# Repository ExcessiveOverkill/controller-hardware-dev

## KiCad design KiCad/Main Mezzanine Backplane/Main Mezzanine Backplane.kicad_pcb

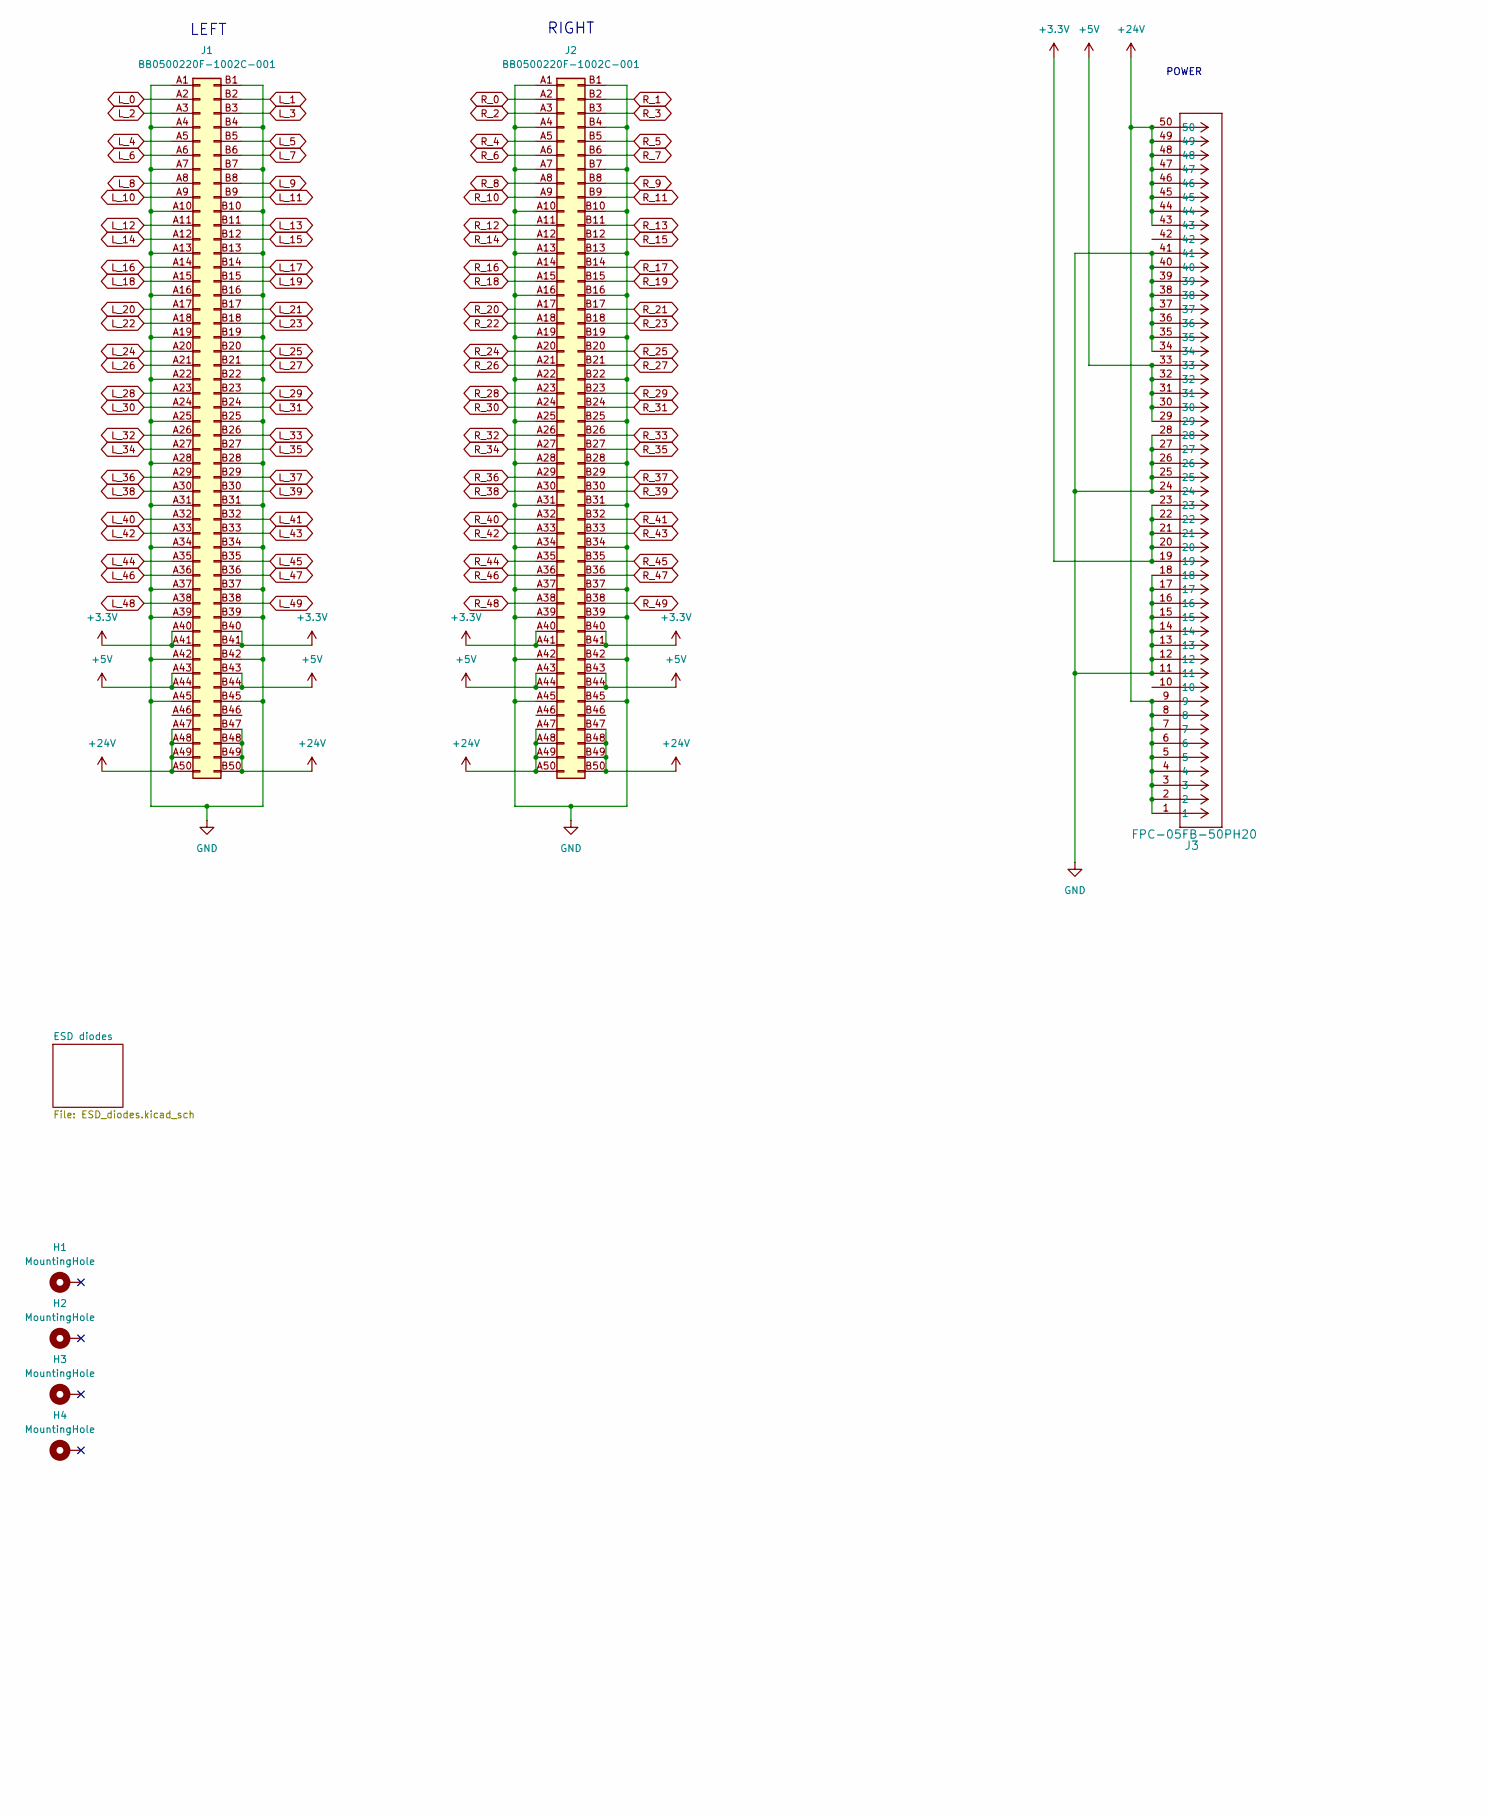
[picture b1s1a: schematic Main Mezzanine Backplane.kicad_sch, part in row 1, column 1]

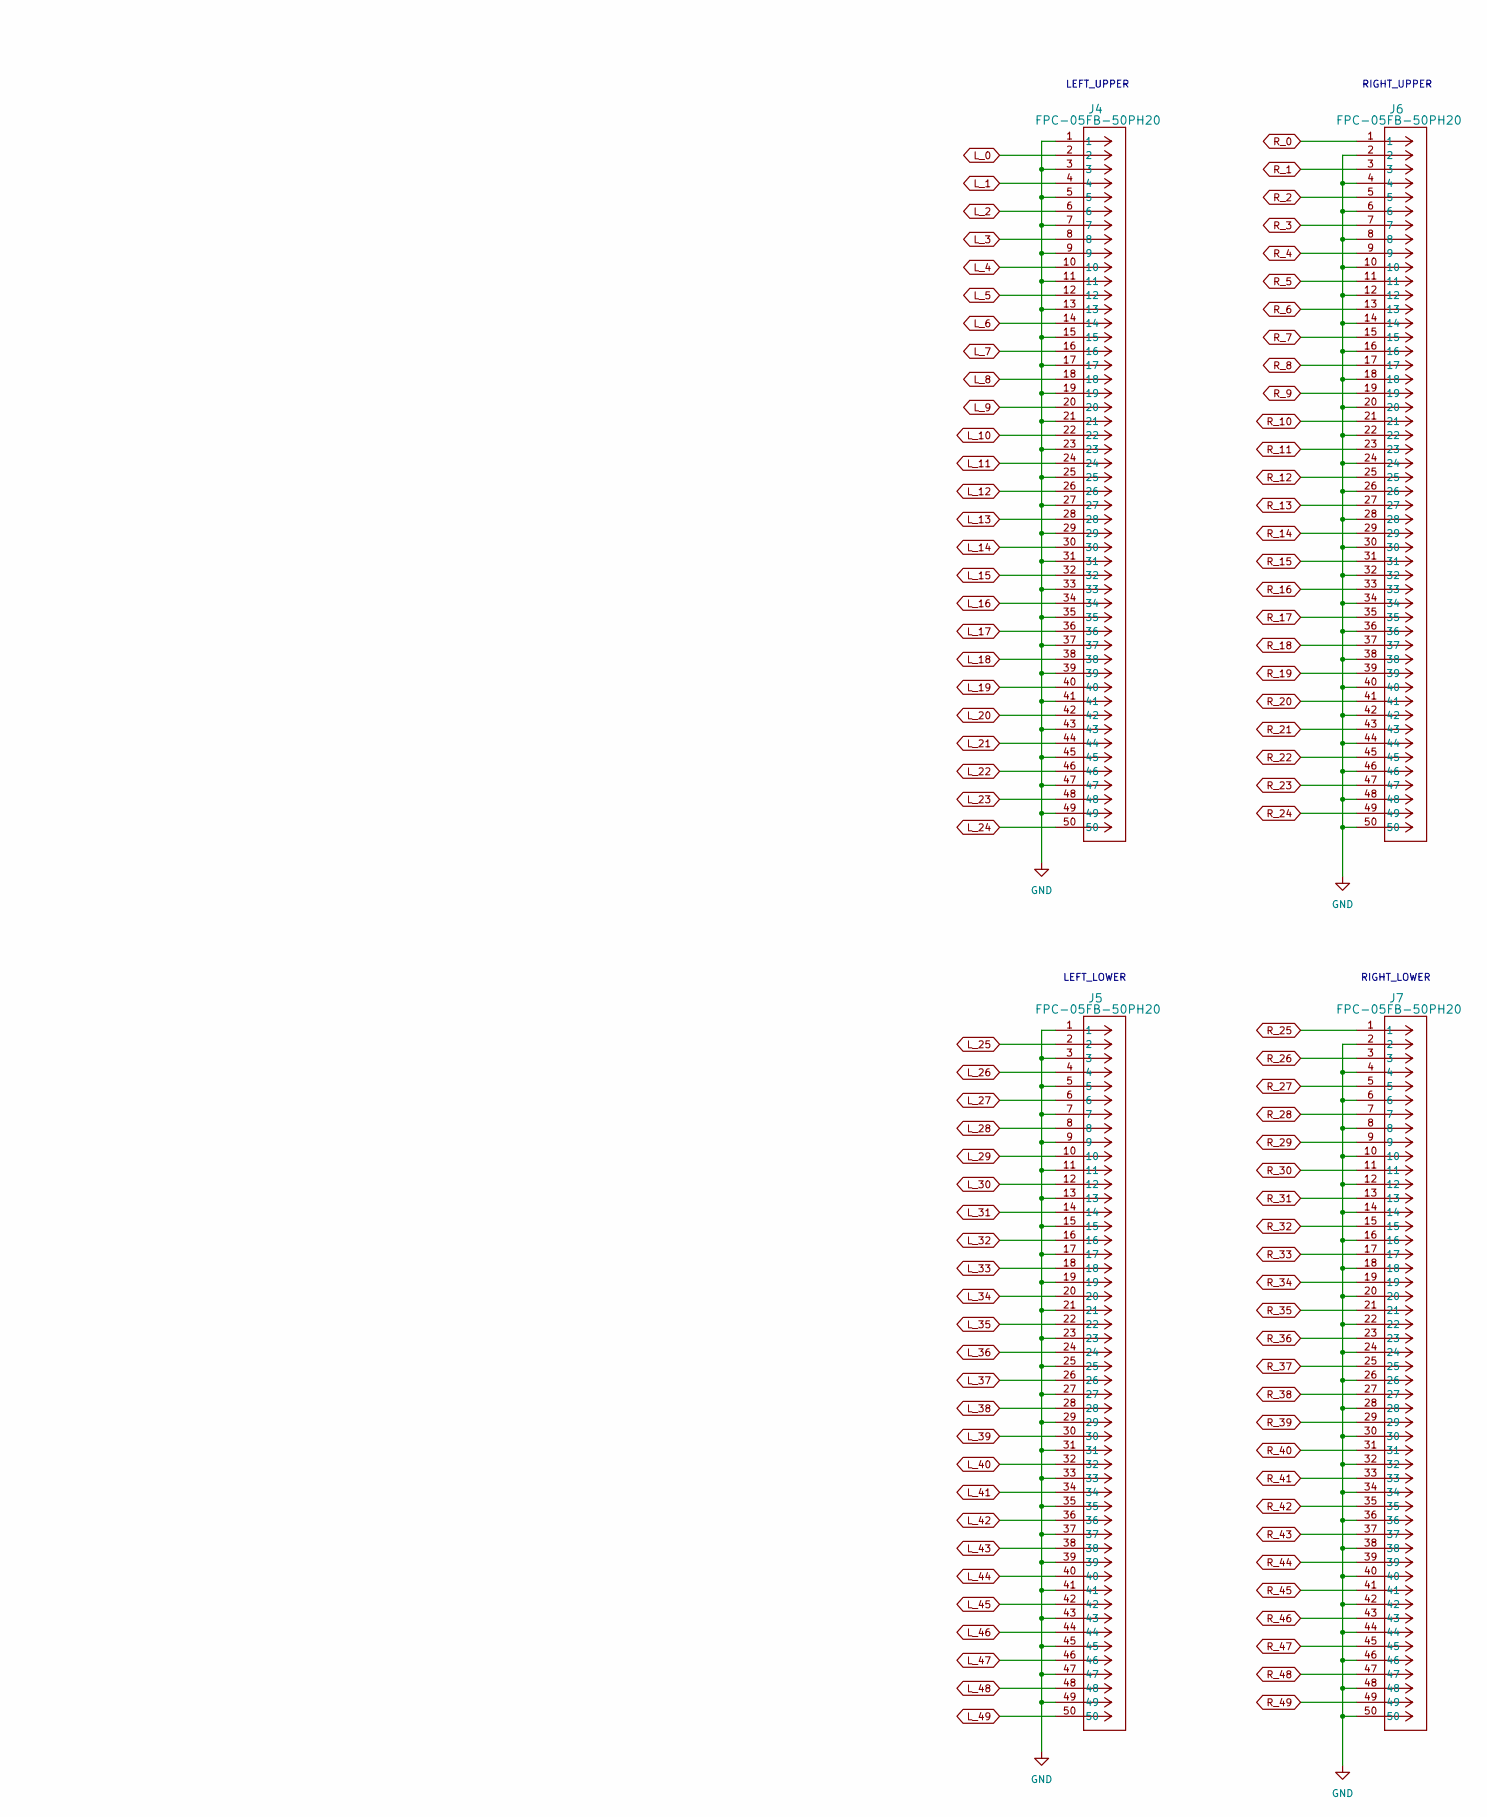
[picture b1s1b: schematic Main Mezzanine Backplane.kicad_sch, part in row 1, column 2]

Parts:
H1, H2, H3, H4: MountingHole; MountingHole_3.2mm_M3_Pad_TopBottom
J1, J2: BB0500220F-1002C-001; Part Number BB0500220F-1002C-001; LCSC# C42421167
J3, J4, J5, J6, J7: FPC-05FB-50PH20; CONN50_FPC-05FB-50PH20_XNP

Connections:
+3.3V: J1.A40, J1.A41, J1.B40, J1.B41, J2.A40, J2.A41, J2.B40, J2.B41, J3.19, J3.20, J3.21, J3.22, J3.23; also elsewhere on the board
+5V: J1.A43, J1.A44, J1.B43, J1.B44, J2.A43, J2.A44, J2.B43, J2.B44, J3.29, J3.30, J3.31, J3.32, J3.33
+24V: J1.A47, J1.A48, J1.A49, J1.A50, J1.B47, J1.B48, J1.B49, J1.B50, J2.A47, J2.A48, J2.A49, J2.A50, J2.B47, J2.B48, J2.B49, J2.B50, J3.1, J3.2, J3.3, J3.4, J3.5, J3.6, J3.7, J3.8, J3.9, J3.43, J3.44, J3.45, J3.46, J3.47, J3.48, J3.49, J3.50
GND: J1.A1, J1.A4, J1.A7, J1.A10, J1.A13, J1.A16, J1.A19, J1.A22, J1.A25, J1.A28, J1.A31, J1.A34, J1.A37, J1.A39, J1.A42, J1.A45, J1.B1, J1.B4, J1.B7, J1.B10, J1.B13, J1.B16, J1.B19, J1.B22, J1.B25, J1.B28, J1.B31, J1.B34, J1.B37, J1.B39, J1.B42, J1.B45, J2.A1, J2.A4, J2.A7, J2.A10, J2.A13, J2.A16, J2.A19, J2.A22, J2.A25, J2.A28, J2.A31, J2.A34, J2.A37, J2.A39, J2.A42, J2.A45, J2.B1, J2.B4, J2.B7, J2.B10, J2.B13, J2.B16, J2.B19, J2.B22, J2.B25, J2.B28, J2.B31, J2.B34, J2.B37, J2.B39, J2.B42, J2.B45, J3.11, J3.12, J3.13, J3.14, J3.15, J3.16, J3.17, J3.18, J3.24, J3.25, J3.26, J3.27, J3.28, J3.34, J3.35, J3.36, J3.37, J3.38, J3.39, J3.40, J3.41, J4.1, J4.3, J4.5, J4.7, J4.9, J4.11, J4.13, J4.15, J4.17, J4.19, J4.21, J4.23, J4.25, J4.27, J4.29, J4.31, J4.33, J4.35, J4.37, J4.39, J4.41, J4.43, J4.45, J4.47, J4.49, J5.1, J5.3, J5.5, J5.7, J5.9, J5.11, J5.13, J5.15, J5.17, J5.19, J5.21, J5.23, J5.25, J5.27, J5.29, J5.31, J5.33, J5.35, J5.37, J5.39, J5.41, J5.43, J5.45, J5.47, J5.49, J6.2, J6.4, J6.6, J6.8, J6.10, J6.12, J6.14, J6.16, J6.18, J6.20, J6.22, J6.24, J6.26, J6.28, J6.30, J6.32, J6.34, J6.36, J6.38, J6.40, J6.42, J6.44, J6.46, J6.48, J6.50, J7.2, J7.4, J7.6, J7.8, J7.10, J7.12, J7.14, J7.16, J7.18, J7.20, J7.22, J7.24, J7.26, J7.28, J7.30, J7.32, J7.34, J7.36, J7.38, J7.40, J7.42, J7.44, J7.46, J7.48, J7.50; also elsewhere on the board
L_0: J1.A2, J4.2; also elsewhere on the board
L_1: J1.B2, J4.4; also elsewhere on the board
L_2: J1.A3, J4.6; also elsewhere on the board
L_3: J1.B3, J4.8; also elsewhere on the board
L_4: J1.A5, J4.10; also elsewhere on the board
L_5: J1.B5, J4.12; also elsewhere on the board
L_6: J1.A6, J4.14; also elsewhere on the board
L_7: J1.B6, J4.16; also elsewhere on the board
L_8: J1.A8, J4.18; also elsewhere on the board
L_9: J1.B8, J4.20; also elsewhere on the board
L_10: J1.A9, J4.22; also elsewhere on the board
L_11: J1.B9, J4.24; also elsewhere on the board
L_12: J1.A11, J4.26; also elsewhere on the board
L_13: J1.B11, J4.28; also elsewhere on the board
L_14: J1.A12, J4.30; also elsewhere on the board
L_15: J1.B12, J4.32; also elsewhere on the board
L_16: J1.A14, J4.34; also elsewhere on the board
L_17: J1.B14, J4.36; also elsewhere on the board
L_18: J1.A15, J4.38; also elsewhere on the board
L_19: J1.B15, J4.40; also elsewhere on the board
L_20: J1.A17, J4.42; also elsewhere on the board
L_21: J1.B17, J4.44; also elsewhere on the board
L_22: J1.A18, J4.46; also elsewhere on the board
L_23: J1.B18, J4.48; also elsewhere on the board
L_24: J1.A20, J4.50; also elsewhere on the board
L_25: J1.B20, J5.2; also elsewhere on the board
L_26: J1.A21, J5.4; also elsewhere on the board
L_27: J1.B21, J5.6; also elsewhere on the board
L_28: J1.A23, J5.8; also elsewhere on the board
L_29: J1.B23, J5.10; also elsewhere on the board
L_30: J1.A24, J5.12; also elsewhere on the board
L_31: J1.B24, J5.14; also elsewhere on the board
L_32: J1.A26, J5.16; also elsewhere on the board
L_33: J1.B26, J5.18; also elsewhere on the board
L_34: J1.A27, J5.20; also elsewhere on the board
L_35: J1.B27, J5.22; also elsewhere on the board
L_36: J1.A29, J5.24; also elsewhere on the board
L_37: J1.B29, J5.26; also elsewhere on the board
L_38: J1.A30, J5.28; also elsewhere on the board
L_39: J1.B30, J5.30; also elsewhere on the board
L_40: J1.A32, J5.32; also elsewhere on the board
L_41: J1.B32, J5.34; also elsewhere on the board
L_42: J1.A33, J5.36; also elsewhere on the board
L_43: J1.B33, J5.38; also elsewhere on the board
L_44: J1.A35, J5.40; also elsewhere on the board
L_45: J1.B35, J5.42; also elsewhere on the board
L_46: J1.A36, J5.44; also elsewhere on the board
L_47: J1.B36, J5.46; also elsewhere on the board
L_48: J1.A38, J5.48; also elsewhere on the board
L_49: J1.B38, J5.50; also elsewhere on the board
R_0: J2.A2, J6.1; also elsewhere on the board
R_1: J2.B2, J6.3; also elsewhere on the board
R_2: J2.A3, J6.5; also elsewhere on the board
R_3: J2.B3, J6.7; also elsewhere on the board
R_4: J2.A5, J6.9; also elsewhere on the board
R_5: J2.B5, J6.11; also elsewhere on the board
R_6: J2.A6, J6.13; also elsewhere on the board
R_7: J2.B6, J6.15; also elsewhere on the board
R_8: J2.A8, J6.17; also elsewhere on the board
R_9: J2.B8, J6.19; also elsewhere on the board
R_10: J2.A9, J6.21; also elsewhere on the board
R_11: J2.B9, J6.23; also elsewhere on the board
R_12: J2.A11, J6.25; also elsewhere on the board
R_13: J2.B11, J6.27; also elsewhere on the board
R_14: J2.A12, J6.29; also elsewhere on the board
R_15: J2.B12, J6.31; also elsewhere on the board
R_16: J2.A14, J6.33; also elsewhere on the board
R_17: J2.B14, J6.35; also elsewhere on the board
R_18: J2.A15, J6.37; also elsewhere on the board
R_19: J2.B15, J6.39; also elsewhere on the board
R_20: J2.A17, J6.41; also elsewhere on the board
R_21: J2.B17, J6.43; also elsewhere on the board
R_22: J2.A18, J6.45; also elsewhere on the board
R_23: J2.B18, J6.47; also elsewhere on the board
R_24: J2.A20, J6.49; also elsewhere on the board
R_25: J2.B20, J7.1; also elsewhere on the board
R_26: J2.A21, J7.3; also elsewhere on the board
R_27: J2.B21, J7.5; also elsewhere on the board
R_28: J2.A23, J7.7; also elsewhere on the board
R_29: J2.B23, J7.9; also elsewhere on the board
R_30: J2.A24, J7.11; also elsewhere on the board
R_31: J2.B24, J7.13; also elsewhere on the board
R_32: J2.A26, J7.15; also elsewhere on the board
R_33: J2.B26, J7.17; also elsewhere on the board
R_34: J2.A27, J7.19; also elsewhere on the board
R_35: J2.B27, J7.21; also elsewhere on the board
R_36: J2.A29, J7.23; also elsewhere on the board
R_37: J2.B29, J7.25; also elsewhere on the board
R_38: J2.A30, J7.27; also elsewhere on the board
R_39: J2.B30, J7.29; also elsewhere on the board
R_40: J2.A32, J7.31; also elsewhere on the board
R_41: J2.B32, J7.33; also elsewhere on the board
R_42: J2.A33, J7.35; also elsewhere on the board
R_43: J2.B33, J7.37; also elsewhere on the board
R_44: J2.A35, J7.39; also elsewhere on the board
R_45: J2.B35, J7.41; also elsewhere on the board
R_46: J2.A36, J7.43; also elsewhere on the board
R_47: J2.B36, J7.45; also elsewhere on the board
R_48: J2.A38, J7.47; also elsewhere on the board
R_49: J2.B38, J7.49; also elsewhere on the board

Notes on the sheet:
LEFT_UPPER
POWER
LEFT_LOWER
LEFT
RIGHT_UPPER
RIGHT
RIGHT_LOWER

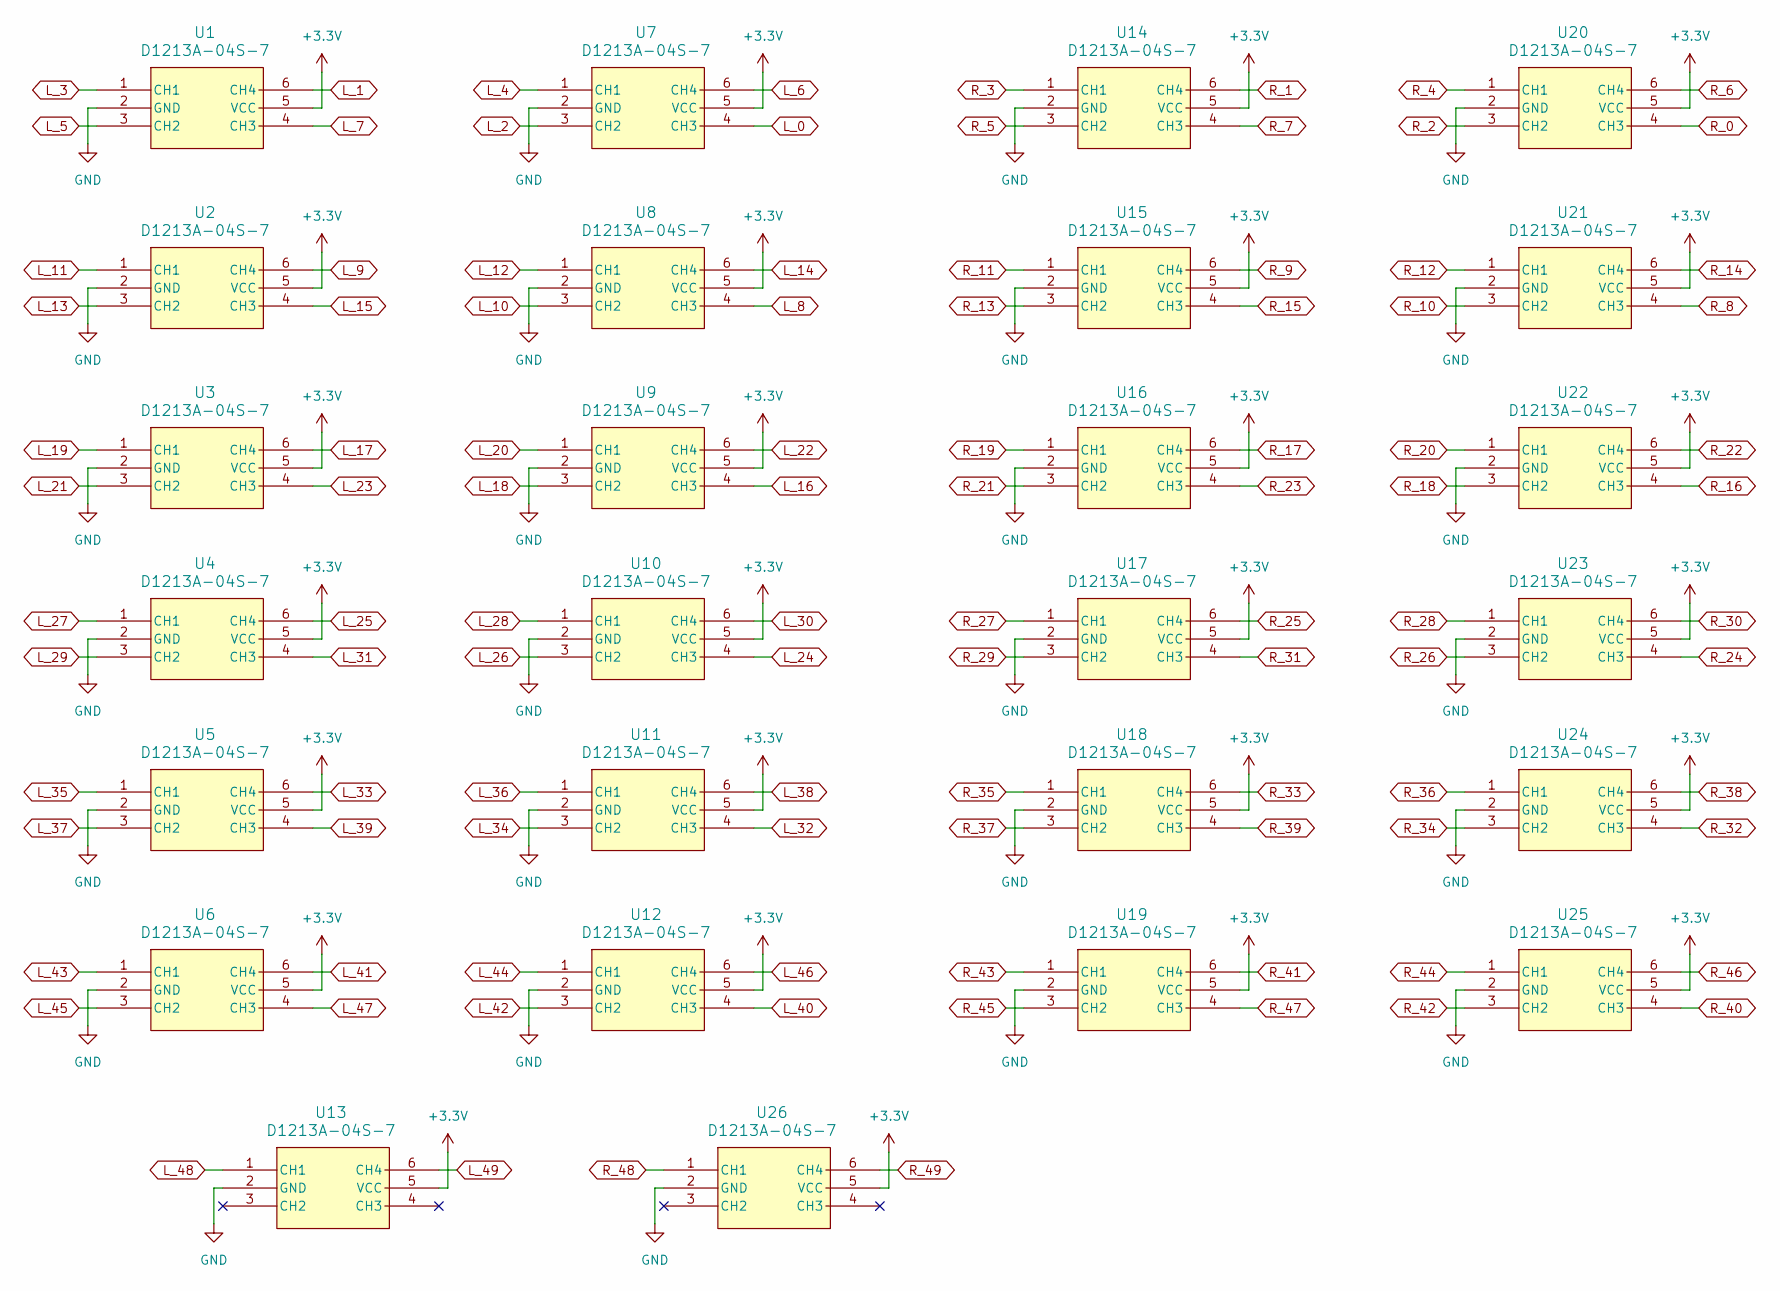
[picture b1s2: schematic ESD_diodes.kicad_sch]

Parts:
U1, U2, U3, U4, U5, U6, U7, U8, U9, U10, U11, U12, U13, U14, U15, U16, U17, U18, U19, U20, U21, U22, U23, U24, U25, U26: D1213A-04S-7; SOT-363_DIO; Part Number D1213A-04S-7-ES; LCSC# C41409235

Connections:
+3.3V: U1.5 (VCC), U2.5 (VCC), U3.5 (VCC), U4.5 (VCC), U5.5 (VCC), U6.5 (VCC), U7.5 (VCC), U8.5 (VCC), U9.5 (VCC), U10.5 (VCC), U11.5 (VCC), U12.5 (VCC), U13.5 (VCC), U14.5 (VCC), U15.5 (VCC), U16.5 (VCC), U17.5 (VCC), U18.5 (VCC), U19.5 (VCC), U20.5 (VCC), U21.5 (VCC), U22.5 (VCC), U23.5 (VCC), U24.5 (VCC), U25.5 (VCC), U26.5 (VCC); also elsewhere on the board
GND: U1.2 (GND), U2.2 (GND), U3.2 (GND), U4.2 (GND), U5.2 (GND), U6.2 (GND), U7.2 (GND), U8.2 (GND), U9.2 (GND), U10.2 (GND), U11.2 (GND), U12.2 (GND), U13.2 (GND), U14.2 (GND), U15.2 (GND), U16.2 (GND), U17.2 (GND), U18.2 (GND), U19.2 (GND), U20.2 (GND), U21.2 (GND), U22.2 (GND), U23.2 (GND), U24.2 (GND), U25.2 (GND), U26.2 (GND); also elsewhere on the board
L_0: U7.4 (CH3); also elsewhere on the board
L_1: U1.6 (CH4); also elsewhere on the board
L_2: U7.3 (CH2); also elsewhere on the board
L_3: U1.1 (CH1); also elsewhere on the board
L_4: U7.1 (CH1); also elsewhere on the board
L_5: U1.3 (CH2); also elsewhere on the board
L_6: U7.6 (CH4); also elsewhere on the board
L_7: U1.4 (CH3); also elsewhere on the board
L_8: U8.4 (CH3); also elsewhere on the board
L_9: U2.6 (CH4); also elsewhere on the board
L_10: U8.3 (CH2); also elsewhere on the board
L_11: U2.1 (CH1); also elsewhere on the board
L_12: U8.1 (CH1); also elsewhere on the board
L_13: U2.3 (CH2); also elsewhere on the board
L_14: U8.6 (CH4); also elsewhere on the board
L_15: U2.4 (CH3); also elsewhere on the board
L_16: U9.4 (CH3); also elsewhere on the board
L_17: U3.6 (CH4); also elsewhere on the board
L_18: U9.3 (CH2); also elsewhere on the board
L_19: U3.1 (CH1); also elsewhere on the board
L_20: U9.1 (CH1); also elsewhere on the board
L_21: U3.3 (CH2); also elsewhere on the board
L_22: U9.6 (CH4); also elsewhere on the board
L_23: U3.4 (CH3); also elsewhere on the board
L_24: U10.4 (CH3); also elsewhere on the board
L_25: U4.6 (CH4); also elsewhere on the board
L_26: U10.3 (CH2); also elsewhere on the board
L_27: U4.1 (CH1); also elsewhere on the board
L_28: U10.1 (CH1); also elsewhere on the board
L_29: U4.3 (CH2); also elsewhere on the board
L_30: U10.6 (CH4); also elsewhere on the board
L_31: U4.4 (CH3); also elsewhere on the board
L_32: U11.4 (CH3); also elsewhere on the board
L_33: U5.6 (CH4); also elsewhere on the board
L_34: U11.3 (CH2); also elsewhere on the board
L_35: U5.1 (CH1); also elsewhere on the board
L_36: U11.1 (CH1); also elsewhere on the board
L_37: U5.3 (CH2); also elsewhere on the board
L_38: U11.6 (CH4); also elsewhere on the board
L_39: U5.4 (CH3); also elsewhere on the board
L_40: U12.4 (CH3); also elsewhere on the board
L_41: U6.6 (CH4); also elsewhere on the board
L_42: U12.3 (CH2); also elsewhere on the board
L_43: U6.1 (CH1); also elsewhere on the board
L_44: U12.1 (CH1); also elsewhere on the board
L_45: U6.3 (CH2); also elsewhere on the board
L_46: U12.6 (CH4); also elsewhere on the board
L_47: U6.4 (CH3); also elsewhere on the board
L_48: U13.1 (CH1); also elsewhere on the board
L_49: U13.6 (CH4); also elsewhere on the board
R_0: U20.4 (CH3); also elsewhere on the board
R_1: U14.6 (CH4); also elsewhere on the board
R_2: U20.3 (CH2); also elsewhere on the board
R_3: U14.1 (CH1); also elsewhere on the board
R_4: U20.1 (CH1); also elsewhere on the board
R_5: U14.3 (CH2); also elsewhere on the board
R_6: U20.6 (CH4); also elsewhere on the board
R_7: U14.4 (CH3); also elsewhere on the board
R_8: U21.4 (CH3); also elsewhere on the board
R_9: U15.6 (CH4); also elsewhere on the board
R_10: U21.3 (CH2); also elsewhere on the board
R_11: U15.1 (CH1); also elsewhere on the board
R_12: U21.1 (CH1); also elsewhere on the board
R_13: U15.3 (CH2); also elsewhere on the board
R_14: U21.6 (CH4); also elsewhere on the board
R_15: U15.4 (CH3); also elsewhere on the board
R_16: U22.4 (CH3); also elsewhere on the board
R_17: U16.6 (CH4); also elsewhere on the board
R_18: U22.3 (CH2); also elsewhere on the board
R_19: U16.1 (CH1); also elsewhere on the board
R_20: U22.1 (CH1); also elsewhere on the board
R_21: U16.3 (CH2); also elsewhere on the board
R_22: U22.6 (CH4); also elsewhere on the board
R_23: U16.4 (CH3); also elsewhere on the board
R_24: U23.4 (CH3); also elsewhere on the board
R_25: U17.6 (CH4); also elsewhere on the board
R_26: U23.3 (CH2); also elsewhere on the board
R_27: U17.1 (CH1); also elsewhere on the board
R_28: U23.1 (CH1); also elsewhere on the board
R_29: U17.3 (CH2); also elsewhere on the board
R_30: U23.6 (CH4); also elsewhere on the board
R_31: U17.4 (CH3); also elsewhere on the board
R_32: U24.4 (CH3); also elsewhere on the board
R_33: U18.6 (CH4); also elsewhere on the board
R_34: U24.3 (CH2); also elsewhere on the board
R_35: U18.1 (CH1); also elsewhere on the board
R_36: U24.1 (CH1); also elsewhere on the board
R_37: U18.3 (CH2); also elsewhere on the board
R_38: U24.6 (CH4); also elsewhere on the board
R_39: U18.4 (CH3); also elsewhere on the board
R_40: U25.4 (CH3); also elsewhere on the board
R_41: U19.6 (CH4); also elsewhere on the board
R_42: U25.3 (CH2); also elsewhere on the board
R_43: U19.1 (CH1); also elsewhere on the board
R_44: U25.1 (CH1); also elsewhere on the board
R_45: U19.3 (CH2); also elsewhere on the board
R_46: U25.6 (CH4); also elsewhere on the board
R_47: U19.4 (CH3); also elsewhere on the board
R_48: U26.1 (CH1); also elsewhere on the board
R_49: U26.6 (CH4); also elsewhere on the board

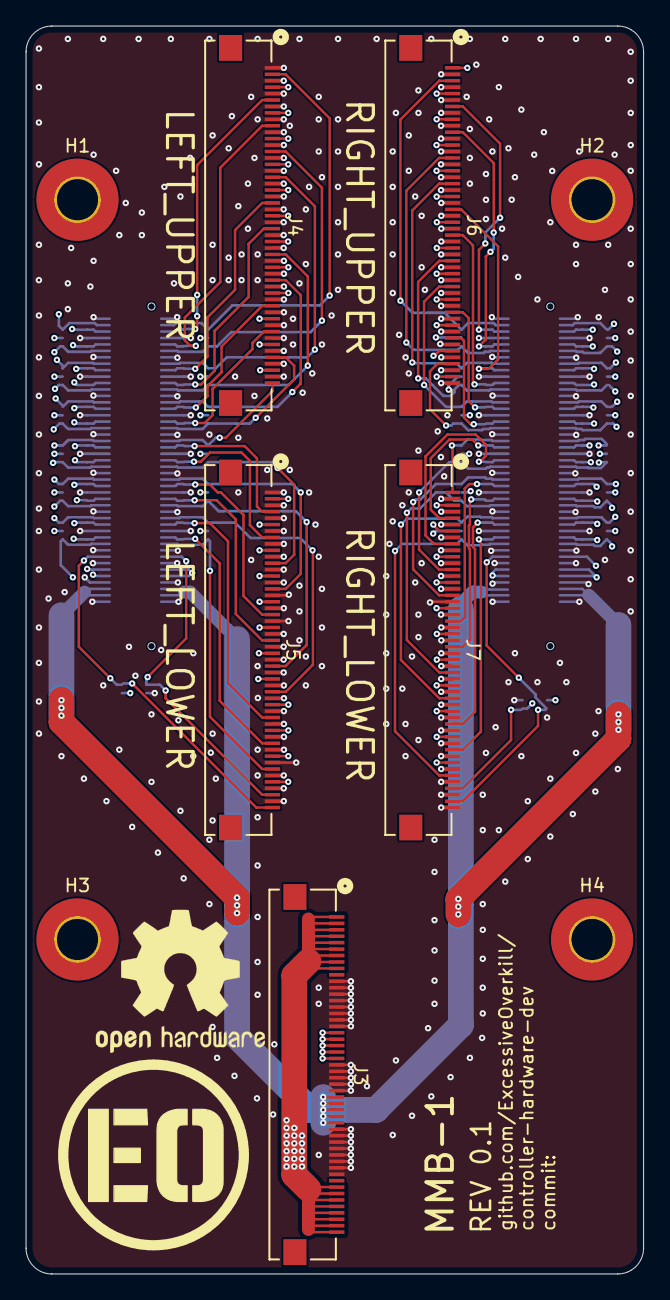
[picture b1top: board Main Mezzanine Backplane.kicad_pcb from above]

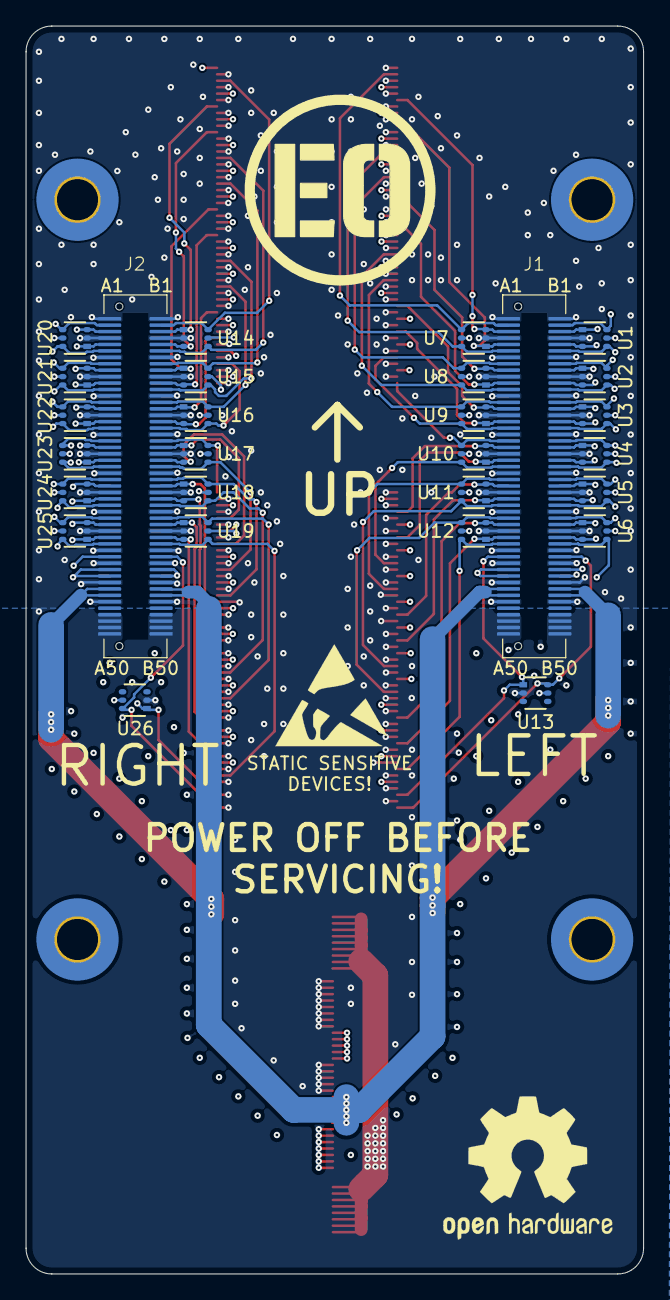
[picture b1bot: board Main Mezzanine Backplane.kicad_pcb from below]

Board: 4 copper layers, 48.0 x 97.0 mm, 37 parts (28 on the bottom side), 104 nets.

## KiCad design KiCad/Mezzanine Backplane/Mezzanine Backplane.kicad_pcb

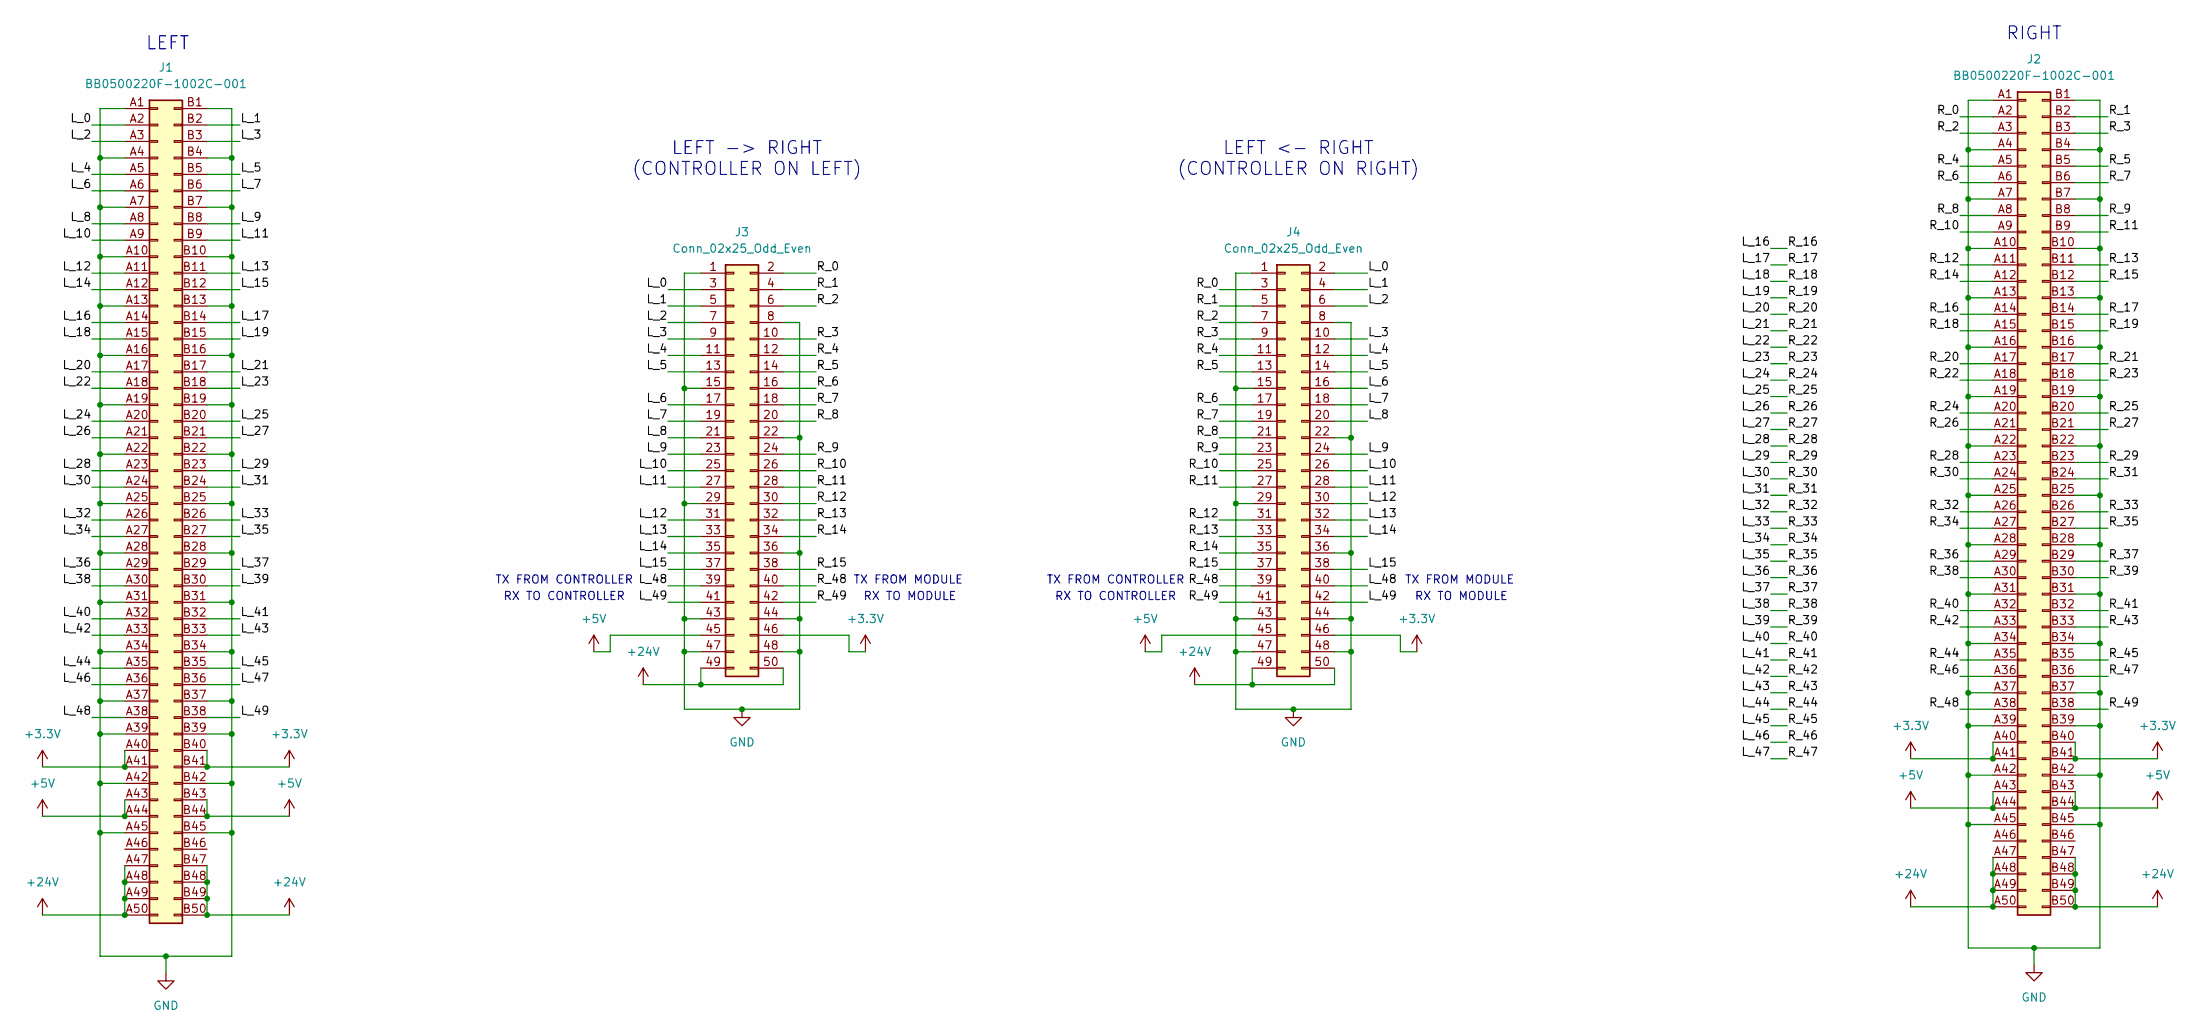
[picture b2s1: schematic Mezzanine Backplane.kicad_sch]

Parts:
J1, J2: BB0500220F-1002C-001; Part Number BB0500220F-1002C-001; LCSC# C42421167
J3, J4: Conn_02x25_Odd_Even; PinSocket_2x25_P2.00mm_Vertical_SMD; Part Number HC-PM200-4.3H-2x25PS; LCSC# C42163108

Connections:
+3.3V: J1.A40, J1.A41, J1.B40, J1.B41, J2.A40, J2.A41, J2.B40, J2.B41, J3.46, J4.46
+5V: J1.A43, J1.A44, J1.B43, J1.B44, J2.A43, J2.A44, J2.B43, J2.B44, J3.45, J4.45
+24V: J1.A47, J1.A48, J1.A49, J1.A50, J1.B47, J1.B48, J1.B49, J1.B50, J2.A47, J2.A48, J2.A49, J2.A50, J2.B47, J2.B48, J2.B49, J2.B50, J3.49, J3.50, J4.49, J4.50
/L_0: J1.A2, J3.3, J4.2
/L_1: J1.B2, J3.5, J4.4
/L_2: J1.A3, J3.7, J4.6
/L_3: J1.B3, J3.9, J4.10
/L_4: J1.A5, J3.11, J4.12
/L_5: J1.B5, J3.13, J4.14
/L_6: J1.A6, J3.17, J4.16
/L_7: J1.B6, J3.19, J4.18
/L_8: J1.A8, J3.21, J4.20
/L_9: J1.B8, J3.23, J4.24
/L_10: J1.A9, J3.25, J4.26
/L_11: J1.B9, J3.27, J4.28
/L_12: J1.A11, J3.31, J4.30
/L_13: J1.B11, J3.33, J4.32
/L_14: J1.A12, J3.35, J4.34
/L_15: J1.B12, J3.37, J4.38
/L_16: J1.A14, J2.A14
/L_17: J1.B14, J2.B14
/L_18: J1.A15, J2.A15
/L_19: J1.B15, J2.B15
/L_20: J1.A17, J2.A17
/L_21: J1.B17, J2.B17
/L_22: J1.A18, J2.A18
/L_23: J1.B18, J2.B18
/L_24: J1.A20, J2.A20
/L_25: J1.B20, J2.B20
/L_26: J1.A21, J2.A21
/L_27: J1.B21, J2.B21
/L_28: J1.A23, J2.A23
/L_29: J1.B23, J2.B23
/L_30: J1.A24, J2.A24
/L_31: J1.B24, J2.B24
/L_32: J1.A26, J2.A26
/L_33: J1.B26, J2.B26
/L_34: J1.A27, J2.A27
/L_35: J1.B27, J2.B27
/L_36: J1.A29, J2.A29
/L_37: J1.B29, J2.B29
/L_38: J1.A30, J2.A30
/L_39: J1.B30, J2.B30
/L_40: J1.A32, J2.A32
/L_41: J1.B32, J2.B32
/L_42: J1.A33, J2.A33
/L_43: J1.B33, J2.B33
/L_44: J1.A35, J2.A35
/L_45: J1.B35, J2.B35
/L_46: J1.A36, J2.A36
/L_47: J1.B36, J2.B36
/L_48: J1.A38, J3.39, J4.40
/L_49: J1.B38, J3.41, J4.42
/R_0: J2.A2, J3.2, J4.3
/R_1: J2.B2, J3.4, J4.5
/R_2: J2.A3, J3.6, J4.7
/R_3: J2.B3, J3.10, J4.9
/R_4: J2.A5, J3.12, J4.11
/R_5: J2.B5, J3.14, J4.13
/R_6: J2.A6, J3.16, J4.17
/R_7: J2.B6, J3.18, J4.19
/R_8: J2.A8, J3.20, J4.21
/R_9: J2.B8, J3.24, J4.23
/R_10: J2.A9, J3.26, J4.25
/R_11: J2.B9, J3.28, J4.27
/R_12: J2.A11, J3.30, J4.31
/R_13: J2.B11, J3.32, J4.33
/R_14: J2.A12, J3.34, J4.35
/R_15: J2.B12, J3.38, J4.37
/R_48: J2.A38, J3.40, J4.39
/R_49: J2.B38, J3.42, J4.41
GND: J1.A1, J1.A4, J1.A7, J1.A10, J1.A13, J1.A16, J1.A19, J1.A22, J1.A25, J1.A28, J1.A31, J1.A34, J1.A37, J1.A39, J1.A42, J1.A45, J1.B1, J1.B4, J1.B7, J1.B10, J1.B13, J1.B16, J1.B19, J1.B22, J1.B25, J1.B28, J1.B31, J1.B34, J1.B37, J1.B39, J1.B42, J1.B45, J2.A1, J2.A4, J2.A7, J2.A10, J2.A13, J2.A16, J2.A19, J2.A22, J2.A25, J2.A28, J2.A31, J2.A34, J2.A37, J2.A39, J2.A42, J2.A45, J2.B1, J2.B4, J2.B7, J2.B10, J2.B13, J2.B16, J2.B19, J2.B22, J2.B25, J2.B28, J2.B31, J2.B34, J2.B37, J2.B39, J2.B42, J2.B45, J3.1, J3.8, J3.15, J3.22, J3.29, J3.36, J3.43, J3.44, J3.47, J3.48, J4.1, J4.8, J4.15, J4.22, J4.29, J4.36, J4.43, J4.44, J4.47, J4.48

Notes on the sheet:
RX TO MODULE
TX FROM MODULE
RIGHT
LEFT
LEFT <- RIGHT (CONTROLLER ON RIGHT)
RX TO CONTROLLER
TX FROM CONTROLLER
LEFT -> RIGHT (CONTROLLER ON LEFT)

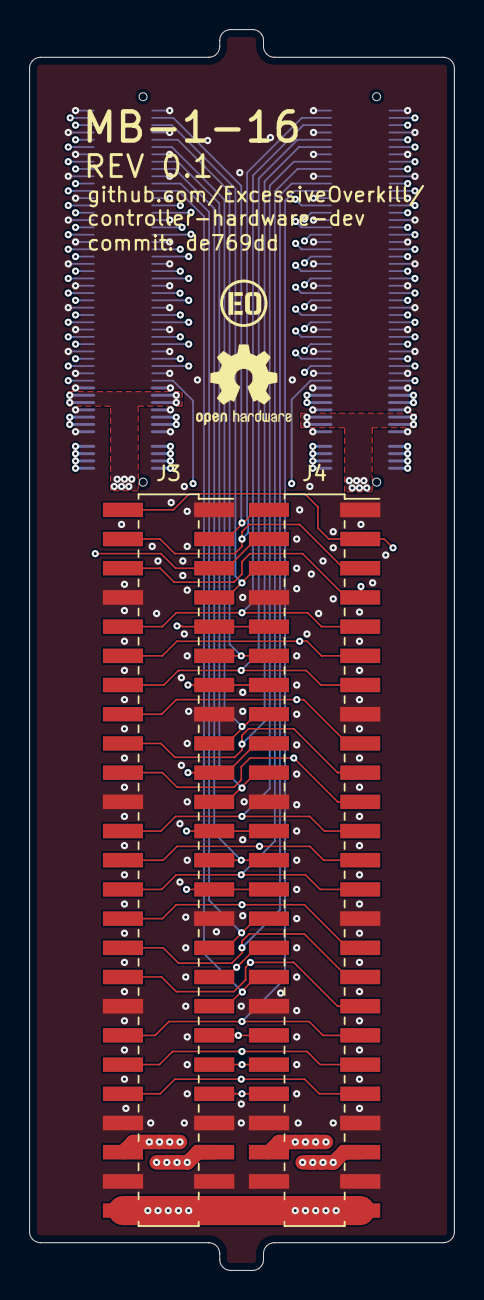
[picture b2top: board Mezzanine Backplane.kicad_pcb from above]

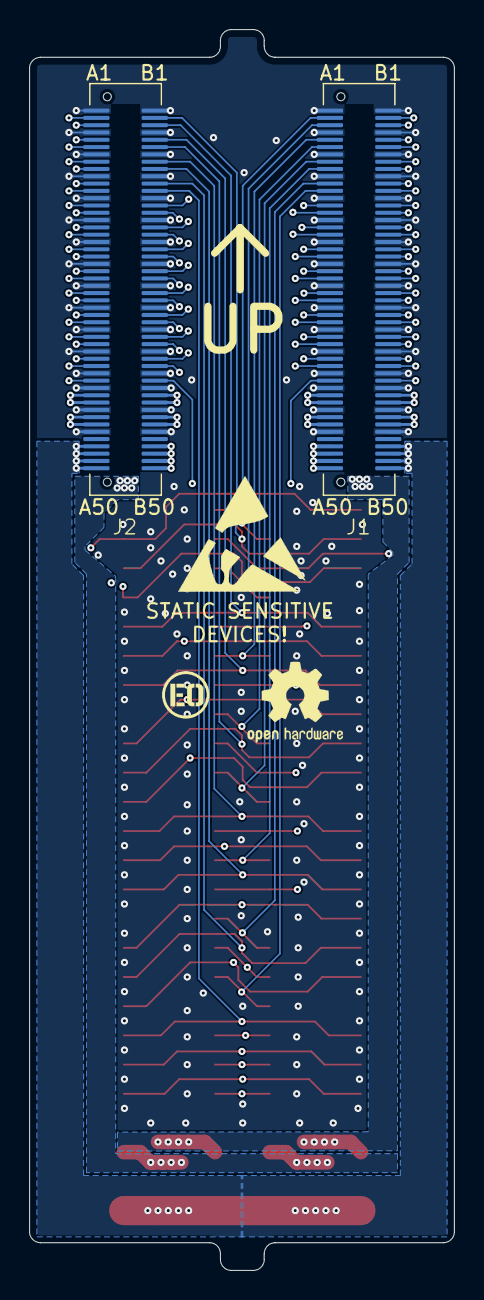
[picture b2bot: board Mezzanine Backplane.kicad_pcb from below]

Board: 4 copper layers, 29.1 x 85.0 mm, 4 parts (2 on the bottom side), 72 nets.
